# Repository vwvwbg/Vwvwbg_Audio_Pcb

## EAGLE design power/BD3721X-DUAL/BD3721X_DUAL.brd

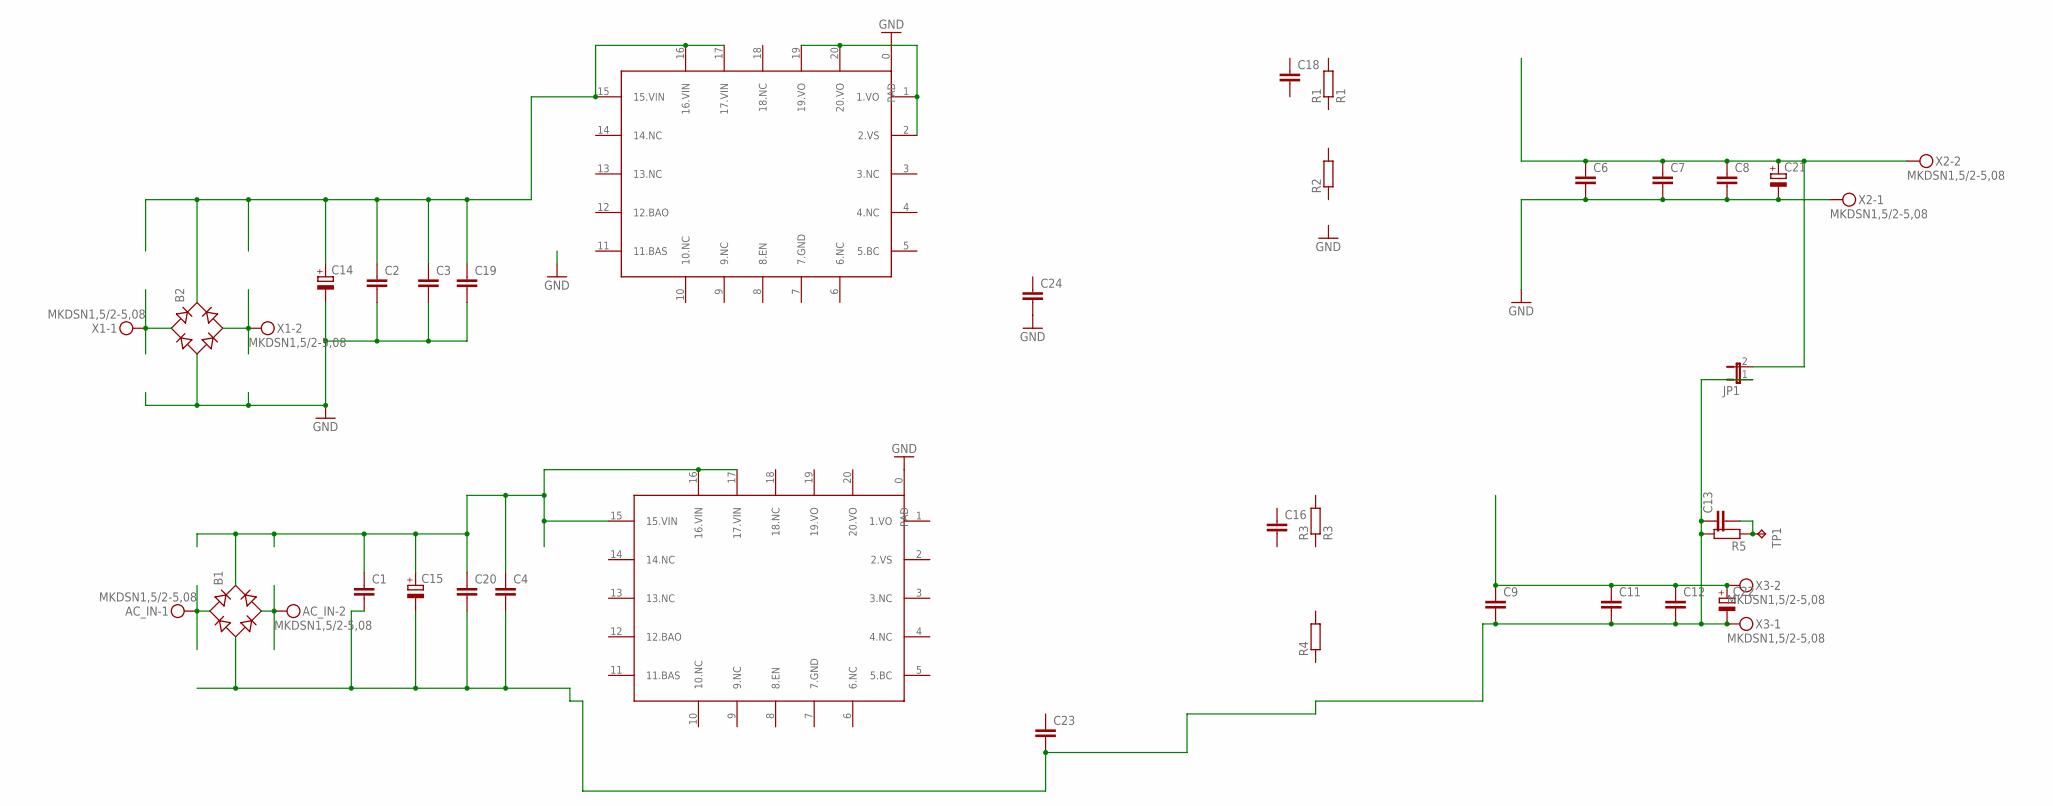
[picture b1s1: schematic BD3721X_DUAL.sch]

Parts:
AC_IN: MKDSN1,5/2-5,08
B1, B2: RB1A
C1, C2, C8, C11: C-EUC1210; C1210
C3, C4, C7, C12: C-EUC0805; C0805
C6, C9, C16, C18, C19, C20, C23, C24: C-EUC0603; C0603
C13: C-EU075-042X103; C075-042X103
C14, C15: CPOL-EUE5-13; E5-13
C21, C22: CPOL-EUE3.5-8; E3,5-8
JP1: JP1E; JP1
R1: R1; R0805
R2, R4: R-EU_R0805; R0805
R3: R3; R0805
R5: R-EU_0207/12; 0207/12
TP1: TPPAD1-13; P1-13
U$1, U$2: BD37210QFN20; QFN20-4X4MM
X1, X2, X3: MKDSN1,5/2-5,08

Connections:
GND: B2.-, C2.2, C3.2, C6.2, C7.2, C8.2, C14.-, C19.2, C21.-, C24.2, U$1.0 (PAD), U$2.0 (PAD), X2.1
GND2: B1.-, C1.2, C4.2, C9.2, C11.2, C12.2, C13.1, C15.-, C20.2, C22.-, C23.2, JP1.1, R5.2, X3.1
unnamed: AC_IN.1, B1.AC1
unnamed: B2.+, C2.1, C3.1, C14.+, C19.1, U$1.15 (15.VIN), U$1.16 (16.VIN), U$1.17 (17.VIN)
unnamed: U$1.1 (1.VO), U$1.2 (2.VS), U$1.19 (19.VO), U$1.20 (20.VO)
unnamed: B2.AC2, X1.2
unnamed: B2.AC1, X1.1
unnamed: AC_IN.2, B1.AC2
unnamed: C13.2, R5.1, TP1.TP
unnamed: B1.+, C1.1, C4.1, C15.+, C20.1, U$2.15 (15.VIN), U$2.16 (16.VIN), U$2.17 (17.VIN)
V+: C6.1, C7.1, C8.1, C21.+, JP1.2, X2.2
V-: C9.1, C11.1, C12.1, C22.+, X3.2

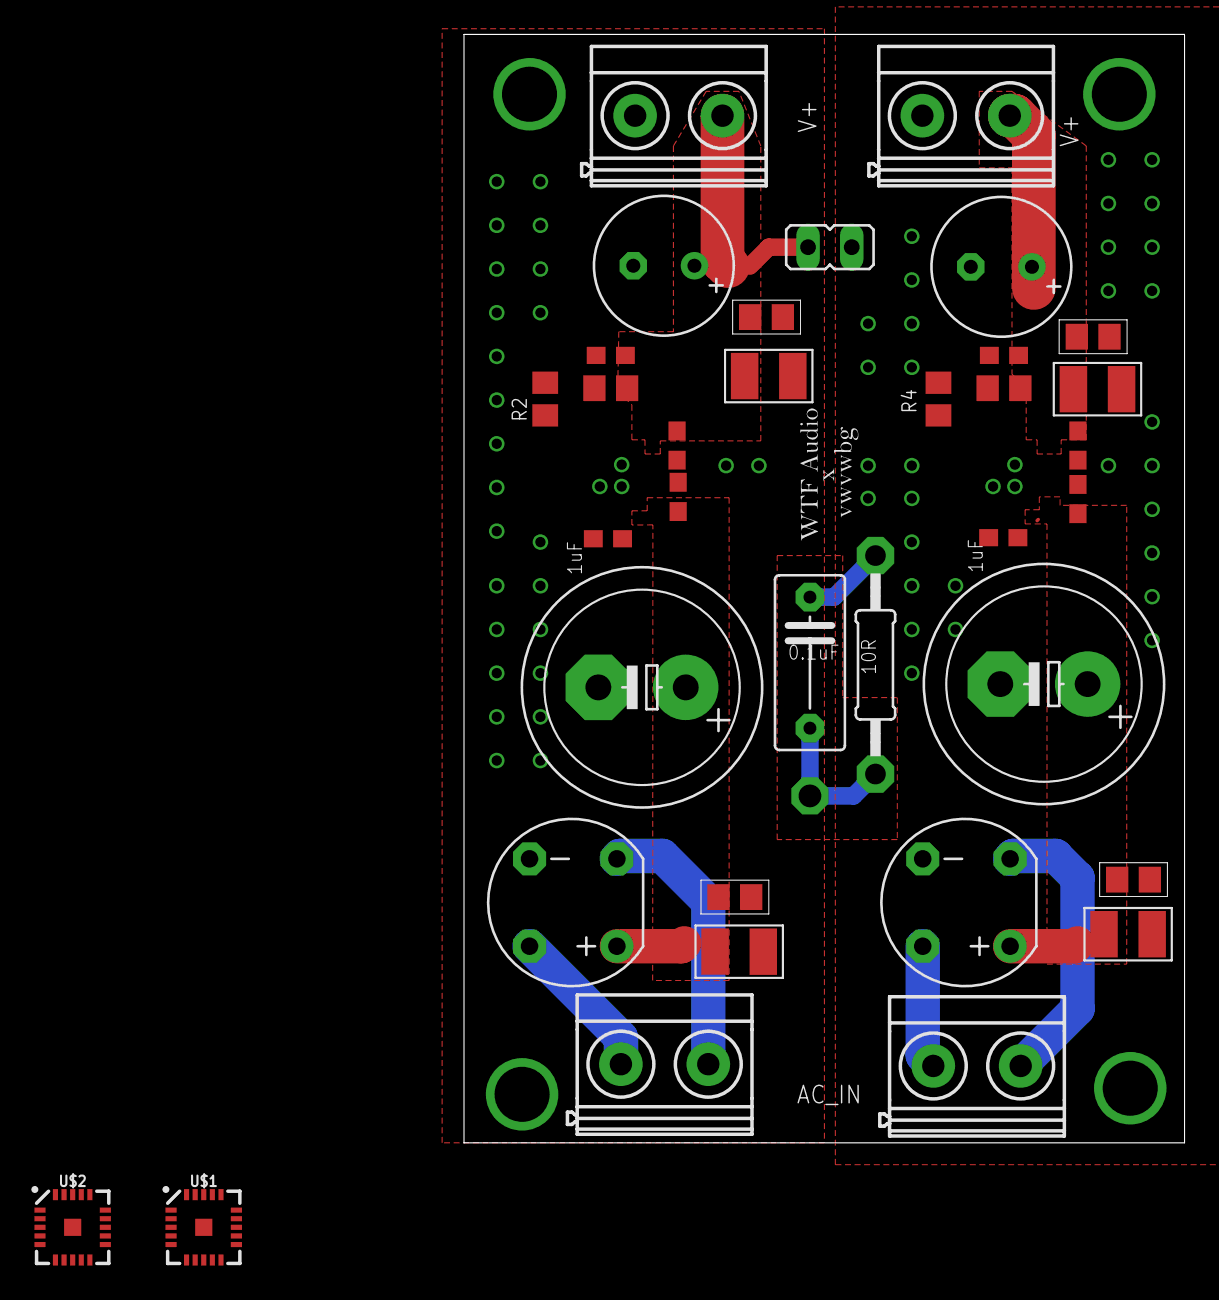
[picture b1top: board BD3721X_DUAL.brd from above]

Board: 2 copper layers, 41.9 x 64.4 mm, 36 parts (0 on the bottom side), 12 nets.

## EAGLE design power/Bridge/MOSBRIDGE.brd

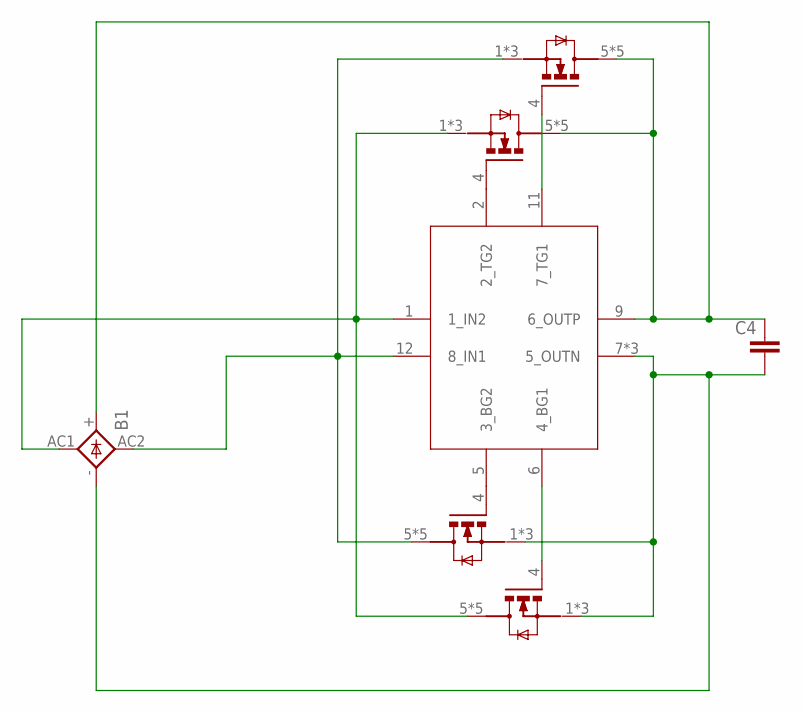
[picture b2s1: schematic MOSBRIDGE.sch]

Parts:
B1: GBU4; GBU4S
C4: 47uF; C1206
Q1, Q2, Q3, Q4: MOS_SMDTDSON-8; PG-TDSON-8
U$1: LT4320MSOP; LT4320_MSOP

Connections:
unnamed: Q2.4 (G), U$1.11 (7_TG1)
unnamed: B1.+, C4.1, Q1.5 (D), Q1.6 (D), Q1.7 (D), Q1.8 (D), Q1.TH (D), Q2.5 (D), Q2.6 (D), Q2.7 (D), Q2.8 (D), Q2.TH (D), U$1.9 (6_OUTP)
unnamed: Q1.4 (G), U$1.2 (2_TG2)
unnamed: Q4.4 (G), U$1.6 (4_BG1)
unnamed: B1.-, C4.2, Q3.1 (S), Q3.2 (S), Q3.3 (S), Q4.1 (S), Q4.2 (S), Q4.3 (S), U$1.7 (5_OUTN), U$1.EXP (5_OUTN), U$1.EXP1 (5_OUTN)
unnamed: B1.AC1 (AC2), Q1.1 (S), Q1.2 (S), Q1.3 (S), Q4.5 (D), Q4.6 (D), Q4.7 (D), Q4.8 (D), Q4.TH (D), U$1.1 (1_IN2)
unnamed: B1.AC2 (AC1), Q2.1 (S), Q2.2 (S), Q2.3 (S), Q3.5 (D), Q3.6 (D), Q3.7 (D), Q3.8 (D), Q3.TH (D), U$1.12 (8_IN1)
unnamed: Q3.4 (G), U$1.5 (3_BG2)

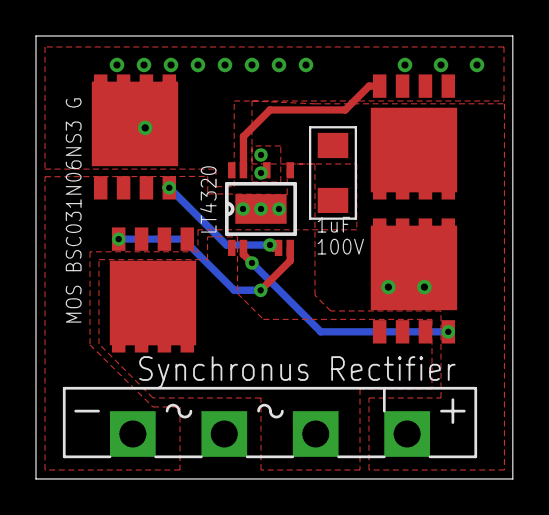
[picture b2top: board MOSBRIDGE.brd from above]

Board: 2 copper layers, 26.5 x 24.6 mm, 7 parts (0 on the bottom side), 8 nets.

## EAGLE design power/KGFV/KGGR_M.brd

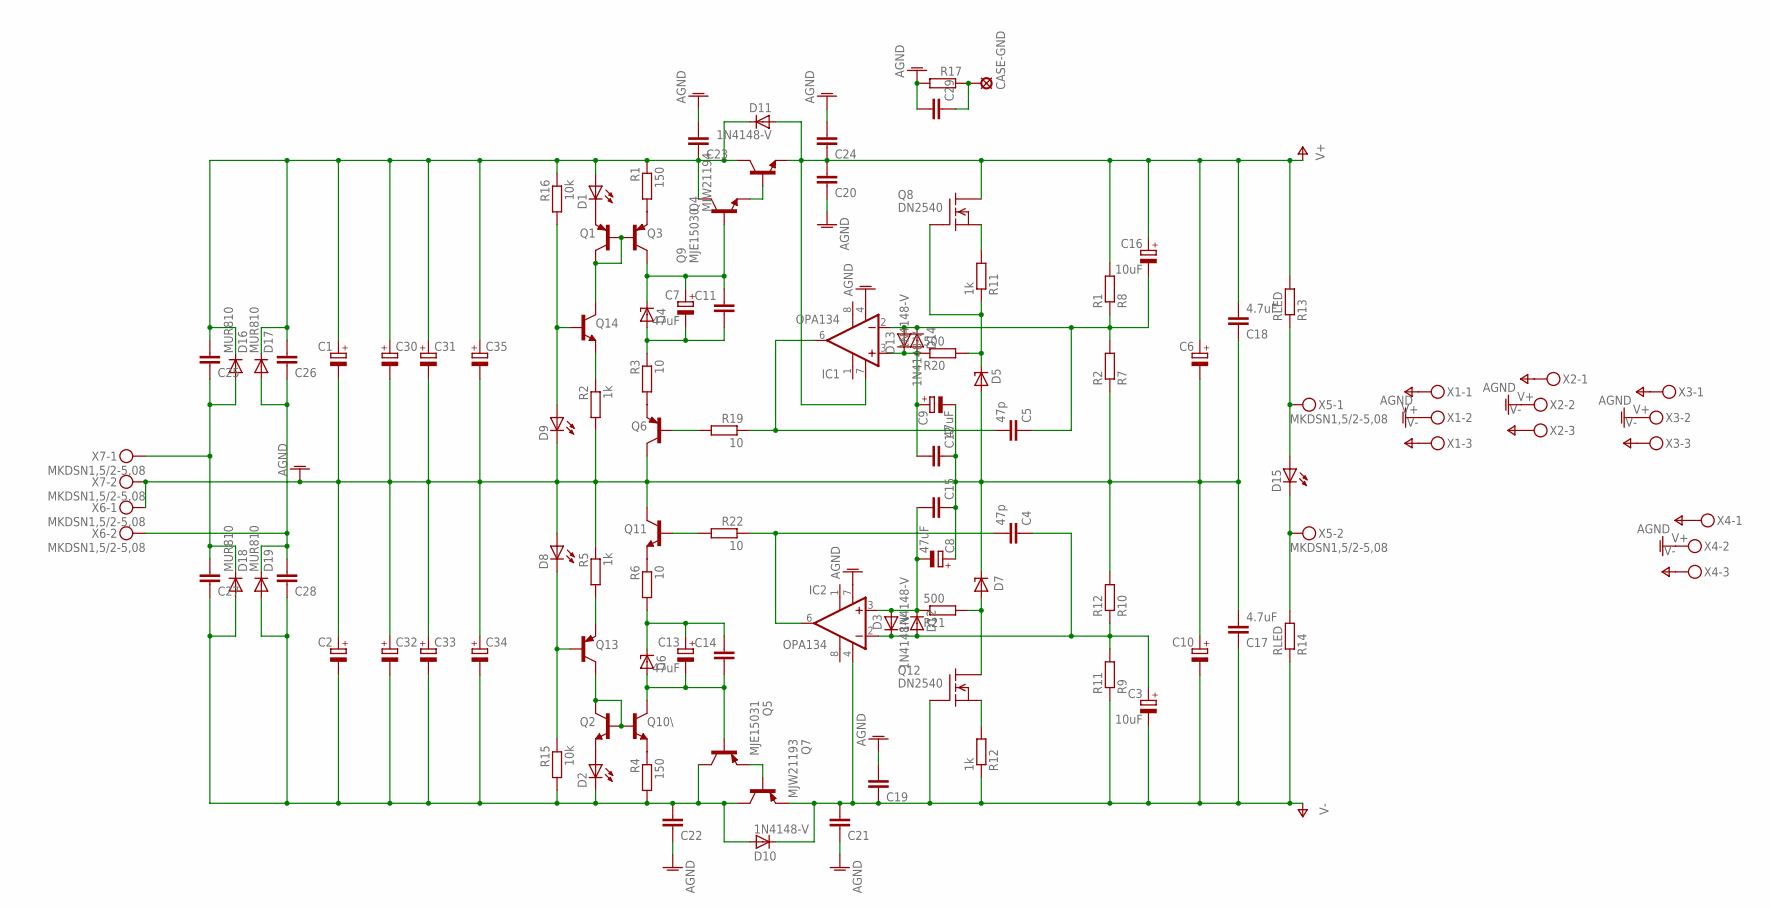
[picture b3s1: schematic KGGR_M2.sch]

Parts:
C1, C2: CPOL-EUE10-35; EB35D
C3, C16: 10uF; E5-8,5
C4, C5: 47p; C025_050-025X075
C6, C10, C30, C31, C32, C33, C34, C35: CPOL-EUE7.5-18; E7,5-18
C7, C8, C9, C13: 47uF; E5-8,5
C11, C12, C14, C15, C19, C20, C21, C24, C25, C26, C27, C28: C-EU050-035X075; C050-035X075
C17, C18: 4.7uF; C050-075X075
C22, C23: C-EU050-075X075; C050-075X075
C29: C-EU102_152-062X184; C102_152-062X184
CASE-GND: SE14
D1, D2, D8, D9, D15: LED5MM
D3, D10, D11, D12, D13, D14: 1N4148-V; 1N4148
D4, D6: 1N4728; DO41Z10
D5, D7: LT1021; DIL08
D16, D17, D18, D19: MUR810; TO220ACS
IC1, IC2: OPA134; DIL08
Q1, Q3, Q6, Q13: MPSA92-PNP-TO92-EBC; TO92-EBC
Q2, Q10\, Q11, Q14: MPSA42-NPN-TO92-EBC; TO92-EBC
Q4: MJW21194; TO-264
Q5: MJE15031; TO220KG
Q7: MJW21193; TO-264
Q8, Q12: DN2540; TO92-
Q9: MJE15030; TO220KG
R1, R4: 150; 0309/12
R2, R5, R11, R12: 1k; 0309/12
R3, R6, R19, R22: 10; 0309/12
R7: R2; 0309/12
R8: R1; 0309/12
R9: R11; 0309/12
R10: R12; 0309/12
R13, R14: RLED; 0309/12
R15, R16: 10k; 0309/12
R17: R-EU_0617/22; 0617/22
R20, R21: 500; 0309/12
X1, X2, X3, X4: MKDSN1,5/3-5,08
X5, X6, X7: MKDSN1,5/2-5,08

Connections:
unnamed: Q1.B, Q1.C, Q3.B, Q14.C
unnamed: D1.K (C), Q1.E
unnamed: Q3.E, R1.2
unnamed: C7.+, C11.1, D4.C, Q3.C, Q9.1 (B)
unnamed: C7.-, C11.2, D4.A, R3.1
unnamed: Q6.E, R3.2
unnamed: Q14.E, R2.1
unnamed: D9.A, Q14.B, R16.2
unnamed: C8.-, C15.2, D3.A, D12.C, IC2.3 (+IN), R21.1
unnamed: Q13.E, R5.2
unnamed: D8.K (C), Q13.B, R15.1
unnamed: Q11.E, R6.1
unnamed: C13.+, C14.1, D6.C, R6.2
unnamed: C13.-, C14.2, D6.A, Q5.1 (B), Q10\.C
unnamed: Q2.B, Q2.C, Q10\.B, Q13.C
unnamed: Q5.3 (E), Q7.B
unnamed: Q10\.E, R4.1
unnamed: D2.A, Q2.E
unnamed: Q4.B, Q9.3 (E)
unnamed: C5.2, C5.3 (2), IC1.6 (OUT), R19.1
unnamed: C4.2, C4.3 (2), IC2.6 (OUT), R22.1
unnamed: Q11.B, R22.2
unnamed: Q6.B, R19.2
unnamed: C5.1, C16.-, D13.A, D14.C, IC1.2 (-IN), R7.2, R8.1
unnamed: Q12.3 (S), R12.2
unnamed: D5.6 (OUT), Q8.2 (G), R11.1, R20.2
unnamed: C9.+, C12.2, D13.C, D14.A, IC1.3 (+IN), R20.1
unnamed: D15.K (C), R14.2, X5.2
unnamed: D7.4 (GND), Q12.1 (D), R21.2
unnamed: C3.+, C4.1, D3.C, D12.A, IC2.2 (-IN), R9.2, R10.1
unnamed: Q8.3 (S), R11.2
unnamed: D15.A, R13.1, X5.1
unnamed: C29.1, CASE-GND.MP, R17.1
V+: C6.+, C16.+, C18.2, C20.2, C24.1, D11.A, IC1.7 (V+), Q4.E, Q8.1 (D), R8.2, R13.2, X1.1, X2.1, X3.1, X4.1
V-: C3.-, C10.-, C17.1, C19.1, C21.2, D10.C, IC2.4 (V-), Q7.E, Q12.2 (G), R9.1, R12.1, R14.1, X1.3, X2.3, X3.3, X4.3

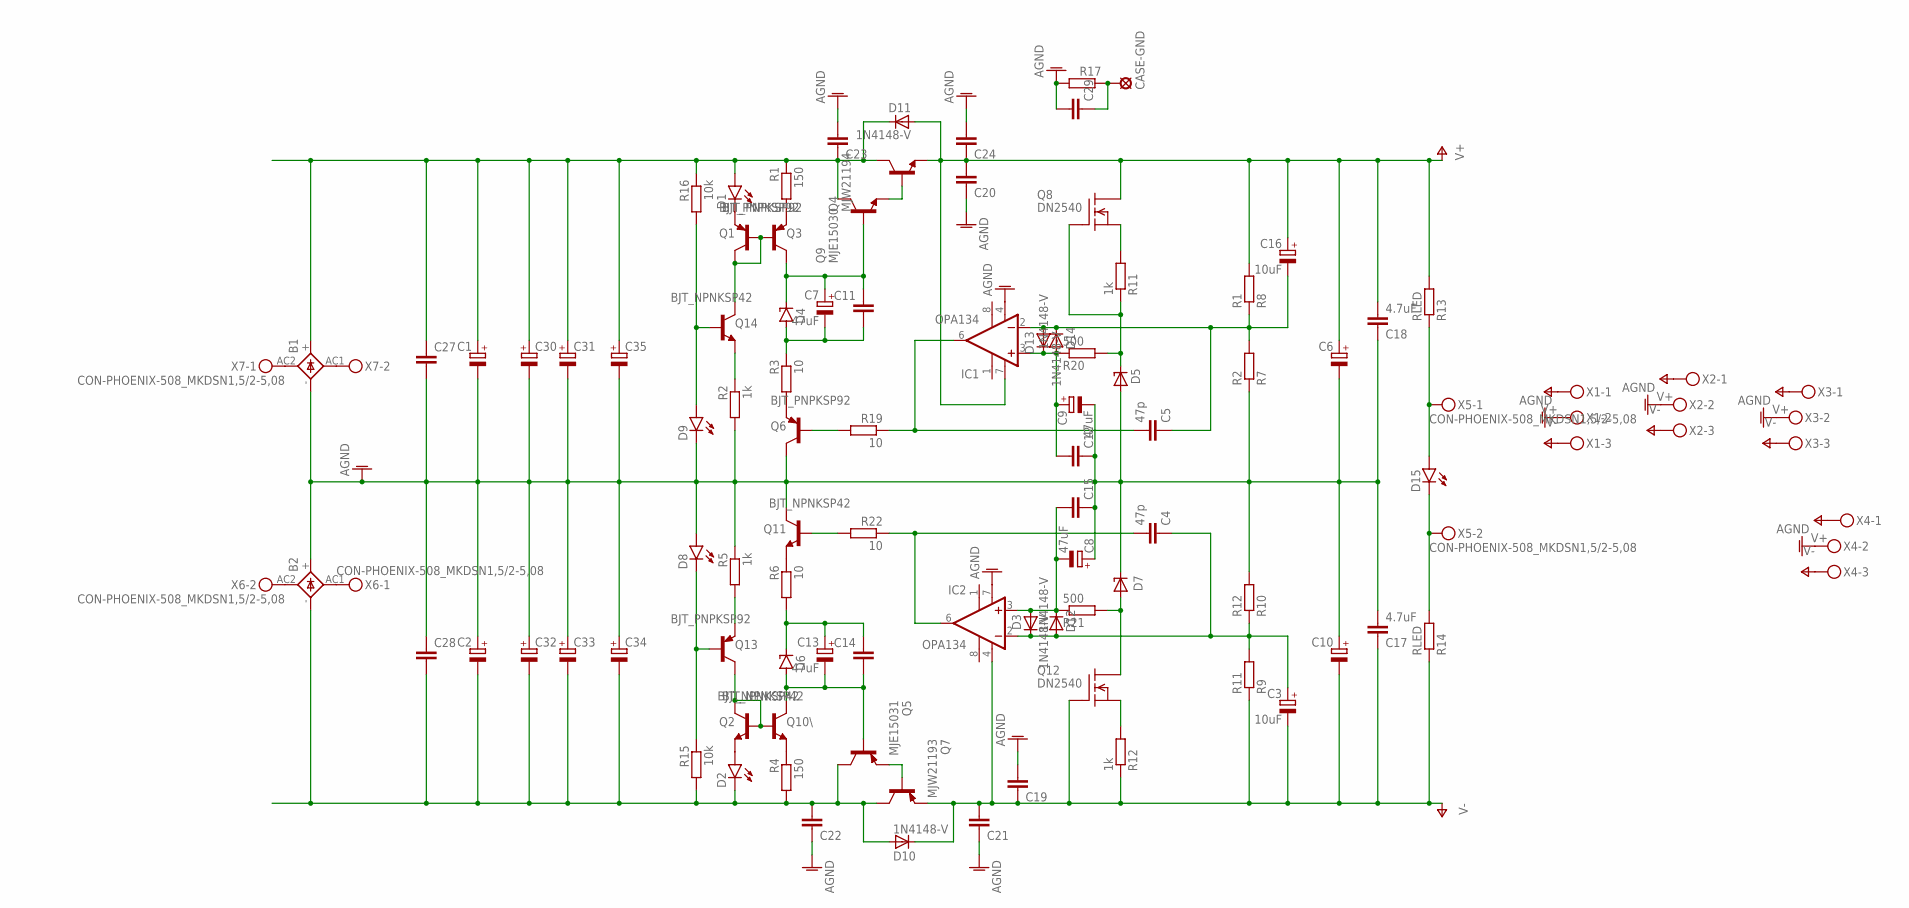
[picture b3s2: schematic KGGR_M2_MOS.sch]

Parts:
B1, B2: GBU4; GBU4S
C1, C2: CPOL-EUE10-35; EB35D
C3, C16: 10uF; E5-8,5
C4, C5: 47p; C025_050-025X075
C6, C10, C30, C31, C32, C33, C34, C35: CPOL-EUE7.5-18; E7,5-18
C7, C8, C9, C13: 47uF; E5-8,5
C11, C12, C14, C15, C19, C20, C21, C24: C-EU050-035X075; C050-035X075
C17, C18: 4.7uF; C050-075X075
C22, C23: C-EU050-075X075; C050-075X075
C27, C28, C29: C-EU102_152-062X184; C102_152-062X184
CASE-GND: SE14
D1, D2, D8, D9, D15: LED5MM
D3, D10, D11, D12, D13, D14: 1N4148-V; 1N4148
D4, D6: 1N4728; DO41Z10
D5, D7: LT1021; DIL08
IC1, IC2: OPA134; DIL08
Q1, Q3, Q6, Q13: BJT_PNPKSP92; TRANSISTOR_TO92-EBC_P
Q2, Q10\, Q11, Q14: BJT_NPNKSP42; TRANSISTOR_TO92-EBC_N
Q4: MJW21194; TRANSISTOR_TO247_BCE_N
Q5: MJE15031; TO220KG
Q7: MJW21193; TRANSISTOR_TO247_BCE_P
Q8, Q12: DN2540; TO92-
Q9: MJE15030; TO220KG
R1, R4: 150; 0309/12
R2, R5, R11, R12: 1k; 0309/12
R3, R6, R19, R22: 10; 0309/12
R7: R2; 0309/12
R8: R1; 0309/12
R9: R11; 0309/12
R10: R12; 0309/12
R13, R14: RLED; 0309/12
R15, R16: 10k; 0309/12
R17: R-EU_0617/22; 0617/22
R20, R21: 500; 0309/12
X1, X2, X3, X4: CON-PHOENIX-508_MKDSN1,5/3-5,08
X5, X6, X7: CON-PHOENIX-508_MKDSN1,5/2-5,08

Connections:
unnamed: Q1.B, Q1.C, Q3.B, Q14.C
unnamed: D1.K (C), Q1.E
unnamed: Q3.E, R1.2
unnamed: C7.+, C11.1, D4.C, Q3.C, Q9.1 (B)
unnamed: C7.-, C11.2, D4.A, R3.1
unnamed: Q6.E, R3.2
unnamed: Q14.E, R2.1
unnamed: D9.A, Q14.B, R16.2
unnamed: C8.-, C15.2, D3.A, D12.C, IC2.3 (+IN), R21.1
unnamed: Q13.E, R5.2
unnamed: D8.K (C), Q13.B, R15.1
unnamed: Q11.E, R6.1
unnamed: C13.+, C14.1, D6.C, R6.2
unnamed: C13.-, C14.2, D6.A, Q5.1 (B), Q10\.C
unnamed: Q2.B, Q2.C, Q10\.B, Q13.C
unnamed: Q5.3 (E), Q7.B
unnamed: Q10\.E, R4.1
unnamed: D2.A, Q2.E
unnamed: Q4.B, Q9.3 (E)
unnamed: C5.2, C5.3 (2), IC1.6 (OUT), R19.1
unnamed: C4.2, C4.3 (2), IC2.6 (OUT), R22.1
unnamed: Q11.B, R22.2
unnamed: Q6.B, R19.2
unnamed: C5.1, C16.-, D13.A, D14.C, IC1.2 (-IN), R7.2, R8.1
unnamed: Q12.3 (S), R12.2
unnamed: D5.6 (OUT), Q8.2 (G), R11.1, R20.2
unnamed: C9.+, C12.2, D13.C, D14.A, IC1.3 (+IN), R20.1
unnamed: D15.K (C), R14.2, X5.2
unnamed: D7.4 (GND), Q12.1 (D), R21.2
unnamed: C3.+, C4.1, D3.C, D12.A, IC2.2 (-IN), R9.2, R10.1
unnamed: Q8.3 (S), R11.2
unnamed: D15.A, R13.1, X5.1
unnamed: C29.1, CASE-GND.MP, R17.1
V+: C6.+, C16.+, C18.2, C20.2, C24.1, D11.A, IC1.7 (V+), Q4.E, Q8.1 (D), R8.2, R13.2, X1.1, X2.1, X3.1, X4.1
V-: C3.-, C10.-, C17.1, C19.1, C21.2, D10.C, IC2.4 (V-), Q7.E, Q12.2 (G), R9.1, R12.1, R14.1, X1.3, X2.3, X3.3, X4.3

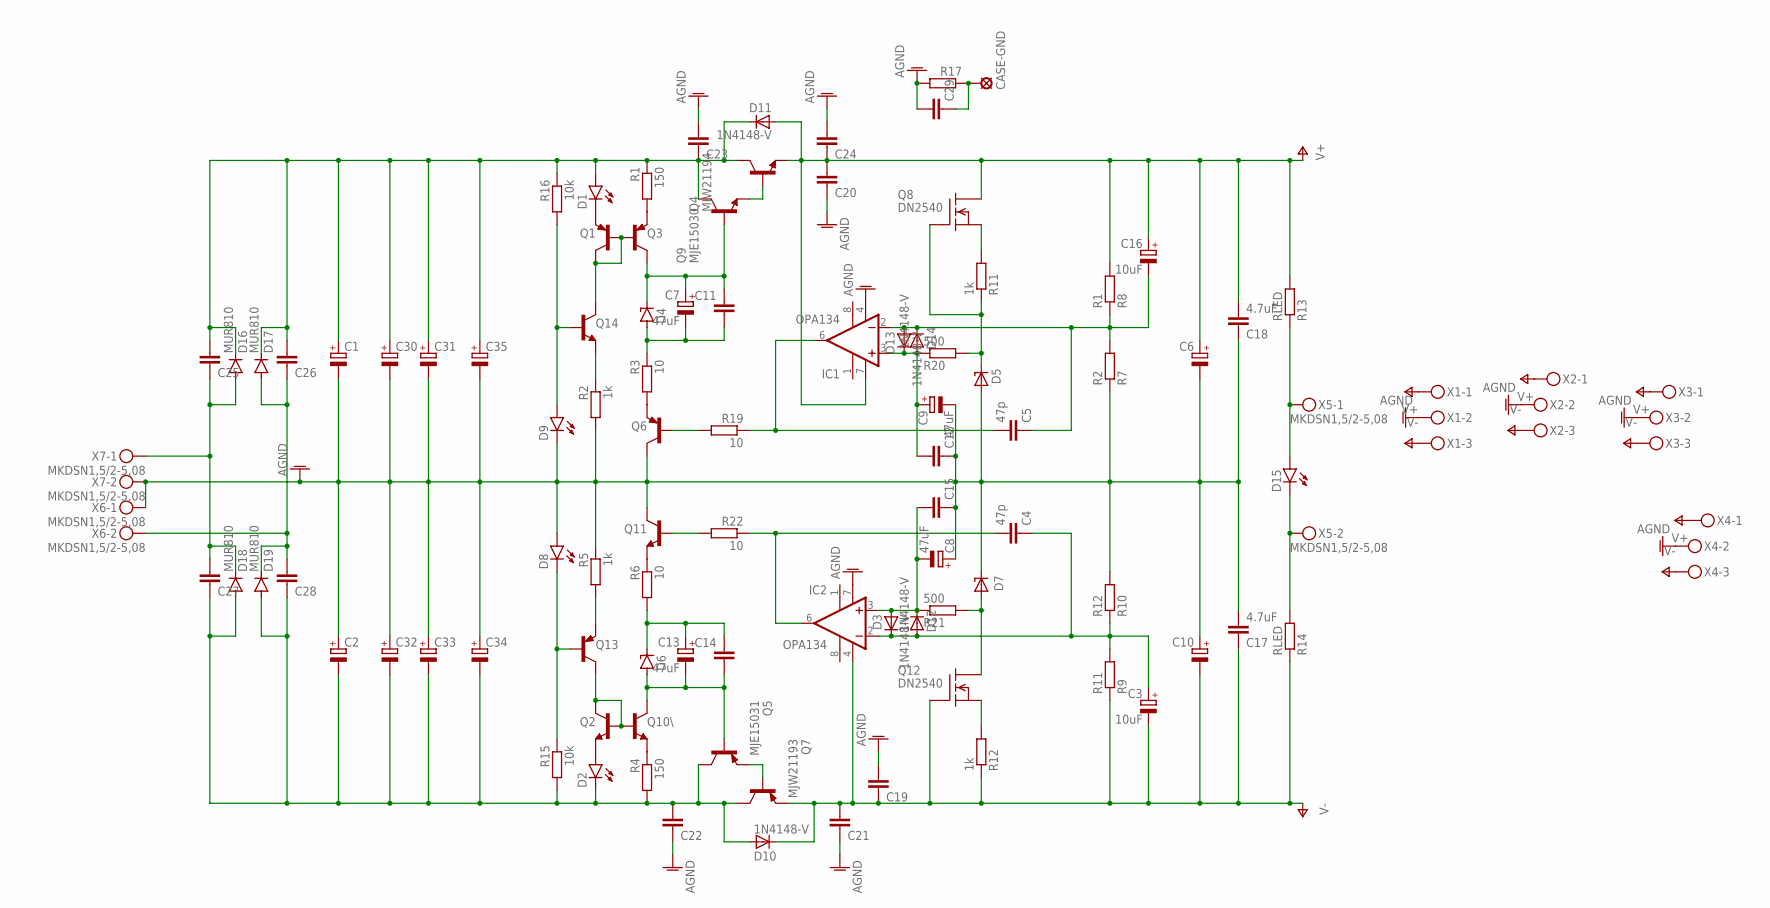
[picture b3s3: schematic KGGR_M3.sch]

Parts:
C1, C2, C6, C10, C30, C31, C32, C33, C34, C35: CPOL-EUE7.5-18; E7,5-18
C3, C16: 10uF; E5-8,5
C4, C5: 47p; C025_050-025X075
C7, C8, C9, C13: 47uF; E5-8,5
C11, C12, C14, C15, C19, C20, C21, C24, C25, C26, C27, C28: C-EU050-035X075; C050-035X075
C17, C18: 4.7uF; C050-075X075
C22, C23: C-EU050-075X075; C050-075X075
C29: C-EU102_152-062X184; C102_152-062X184
CASE-GND: SE14
D1, D2, D8, D9, D15: LED5MM
D3, D10, D11, D12, D13, D14: 1N4148-V; 1N4148
D4, D6: 1N4728; DO41Z10
D5, D7: LT1021; DIL08
D16, D17, D18, D19: MUR810; TO220ACS
IC1, IC2: OPA134; DIL08
Q1, Q3, Q6, Q13: MPSA92-PNP-TO92-EBC; TO92-EBC
Q2, Q10\, Q11, Q14: MPSA42-NPN-TO92-EBC; TO92-EBC
Q4: MJW21194; TO-264
Q5: MJE15031; TO220KG
Q7: MJW21193; TO-264
Q8, Q12: DN2540; TO92-
Q9: MJE15030; TO220KG
R1, R4: 150; 0309/12
R2, R5, R11, R12: 1k; 0309/12
R3, R6, R19, R22: 10; 0309/12
R7: R2; 0309/12
R8: R1; 0309/12
R9: R11; 0309/12
R10: R12; 0309/12
R13, R14: RLED; 0309/12
R15, R16: 10k; 0309/12
R17: R-EU_0617/22; 0617/22
R20, R21: 500; 0309/12
X1, X2, X3, X4: MKDSN1,5/3-5,08
X5, X6, X7: MKDSN1,5/2-5,08

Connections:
unnamed: Q1.B, Q1.C, Q3.B, Q14.C
unnamed: D1.K (C), Q1.E
unnamed: Q3.E, R1.2
unnamed: C7.+, C11.1, D4.C, Q3.C, Q9.1 (B)
unnamed: C7.-, C11.2, D4.A, R3.1
unnamed: Q6.E, R3.2
unnamed: Q14.E, R2.1
unnamed: D9.A, Q14.B, R16.2
unnamed: C8.-, C15.2, D3.A, D12.C, IC2.3 (+IN), R21.1
unnamed: Q13.E, R5.2
unnamed: D8.K (C), Q13.B, R15.1
unnamed: Q11.E, R6.1
unnamed: C13.+, C14.1, D6.C, R6.2
unnamed: C13.-, C14.2, D6.A, Q5.1 (B), Q10\.C
unnamed: Q2.B, Q2.C, Q10\.B, Q13.C
unnamed: Q5.3 (E), Q7.B
unnamed: Q10\.E, R4.1
unnamed: D2.A, Q2.E
unnamed: Q4.B, Q9.3 (E)
unnamed: C5.2, C5.3 (2), IC1.6 (OUT), R19.1
unnamed: C4.2, C4.3 (2), IC2.6 (OUT), R22.1
unnamed: Q11.B, R22.2
unnamed: Q6.B, R19.2
unnamed: C5.1, C16.-, D13.A, D14.C, IC1.2 (-IN), R7.2, R8.1
unnamed: Q12.3 (S), R12.2
unnamed: D5.6 (OUT), Q8.2 (G), R11.1, R20.2
unnamed: C9.+, C12.2, D13.C, D14.A, IC1.3 (+IN), R20.1
unnamed: D15.K (C), R14.2, X5.2
unnamed: D7.4 (GND), Q12.1 (D), R21.2
unnamed: C3.+, C4.1, D3.C, D12.A, IC2.2 (-IN), R9.2, R10.1
unnamed: Q8.3 (S), R11.2
unnamed: D15.A, R13.1, X5.1
unnamed: C29.1, CASE-GND.MP, R17.1
V+: C6.+, C16.+, C18.2, C20.2, C24.1, D11.A, IC1.7 (V+), Q4.E, Q8.1 (D), R8.2, R13.2, X1.1, X2.1, X3.1, X4.1
V-: C3.-, C10.-, C17.1, C19.1, C21.2, D10.C, IC2.4 (V-), Q7.E, Q12.2 (G), R9.1, R12.1, R14.1, X1.3, X2.3, X3.3, X4.3

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
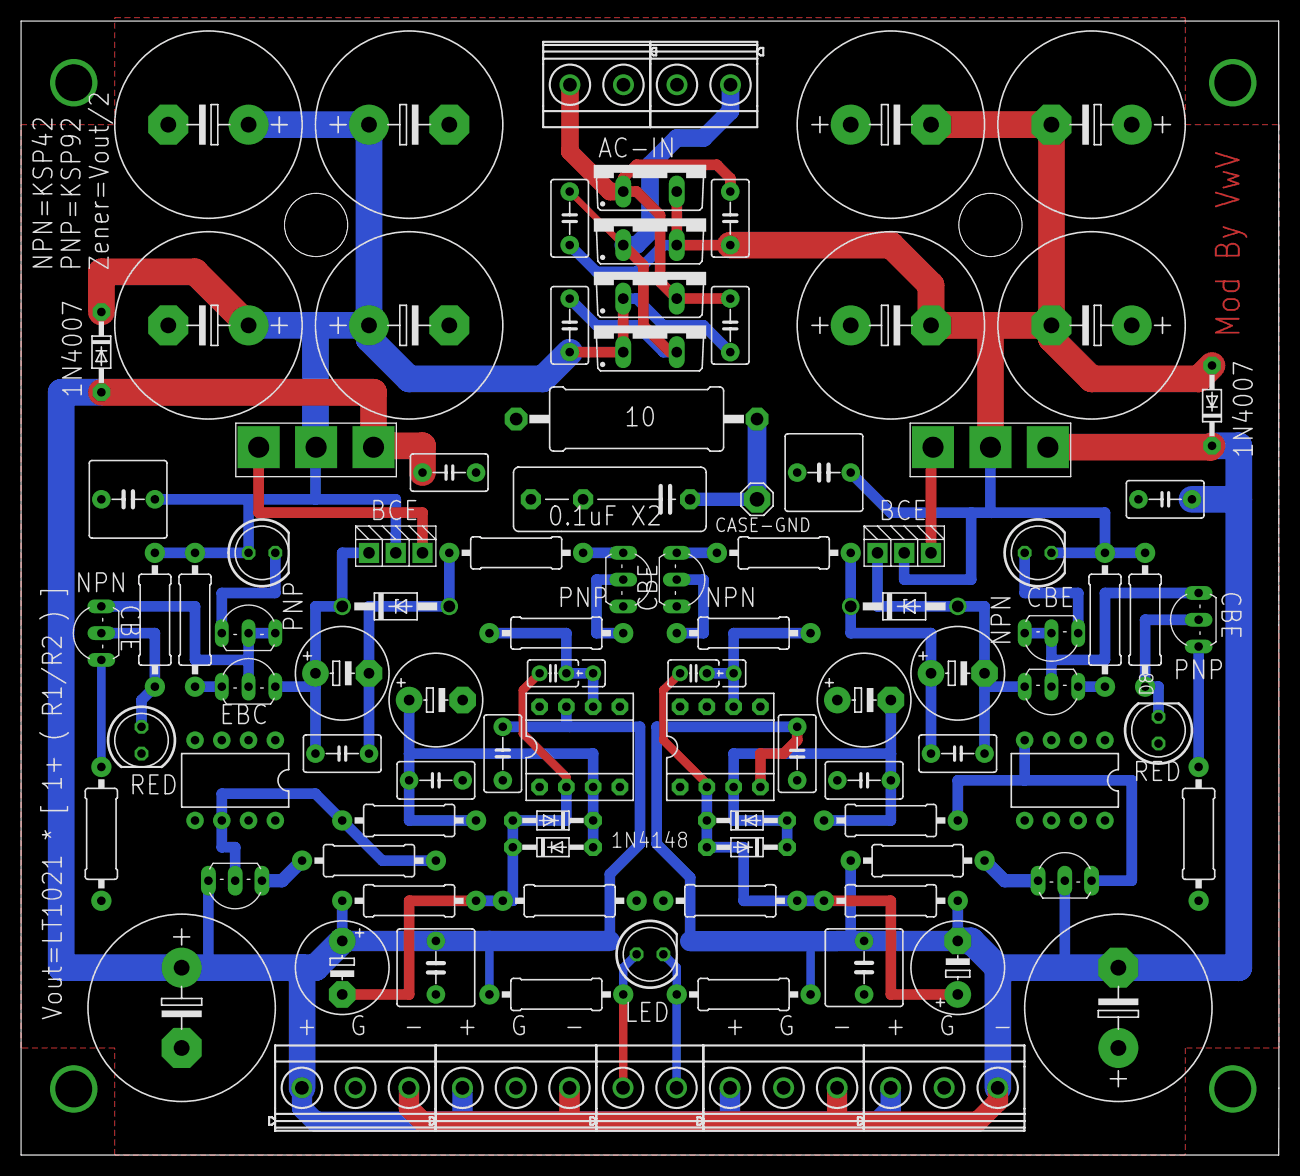
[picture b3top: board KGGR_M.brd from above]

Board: 2 copper layers, 119.4 x 107.6 mm, 99 parts (0 on the bottom side), 40 nets.

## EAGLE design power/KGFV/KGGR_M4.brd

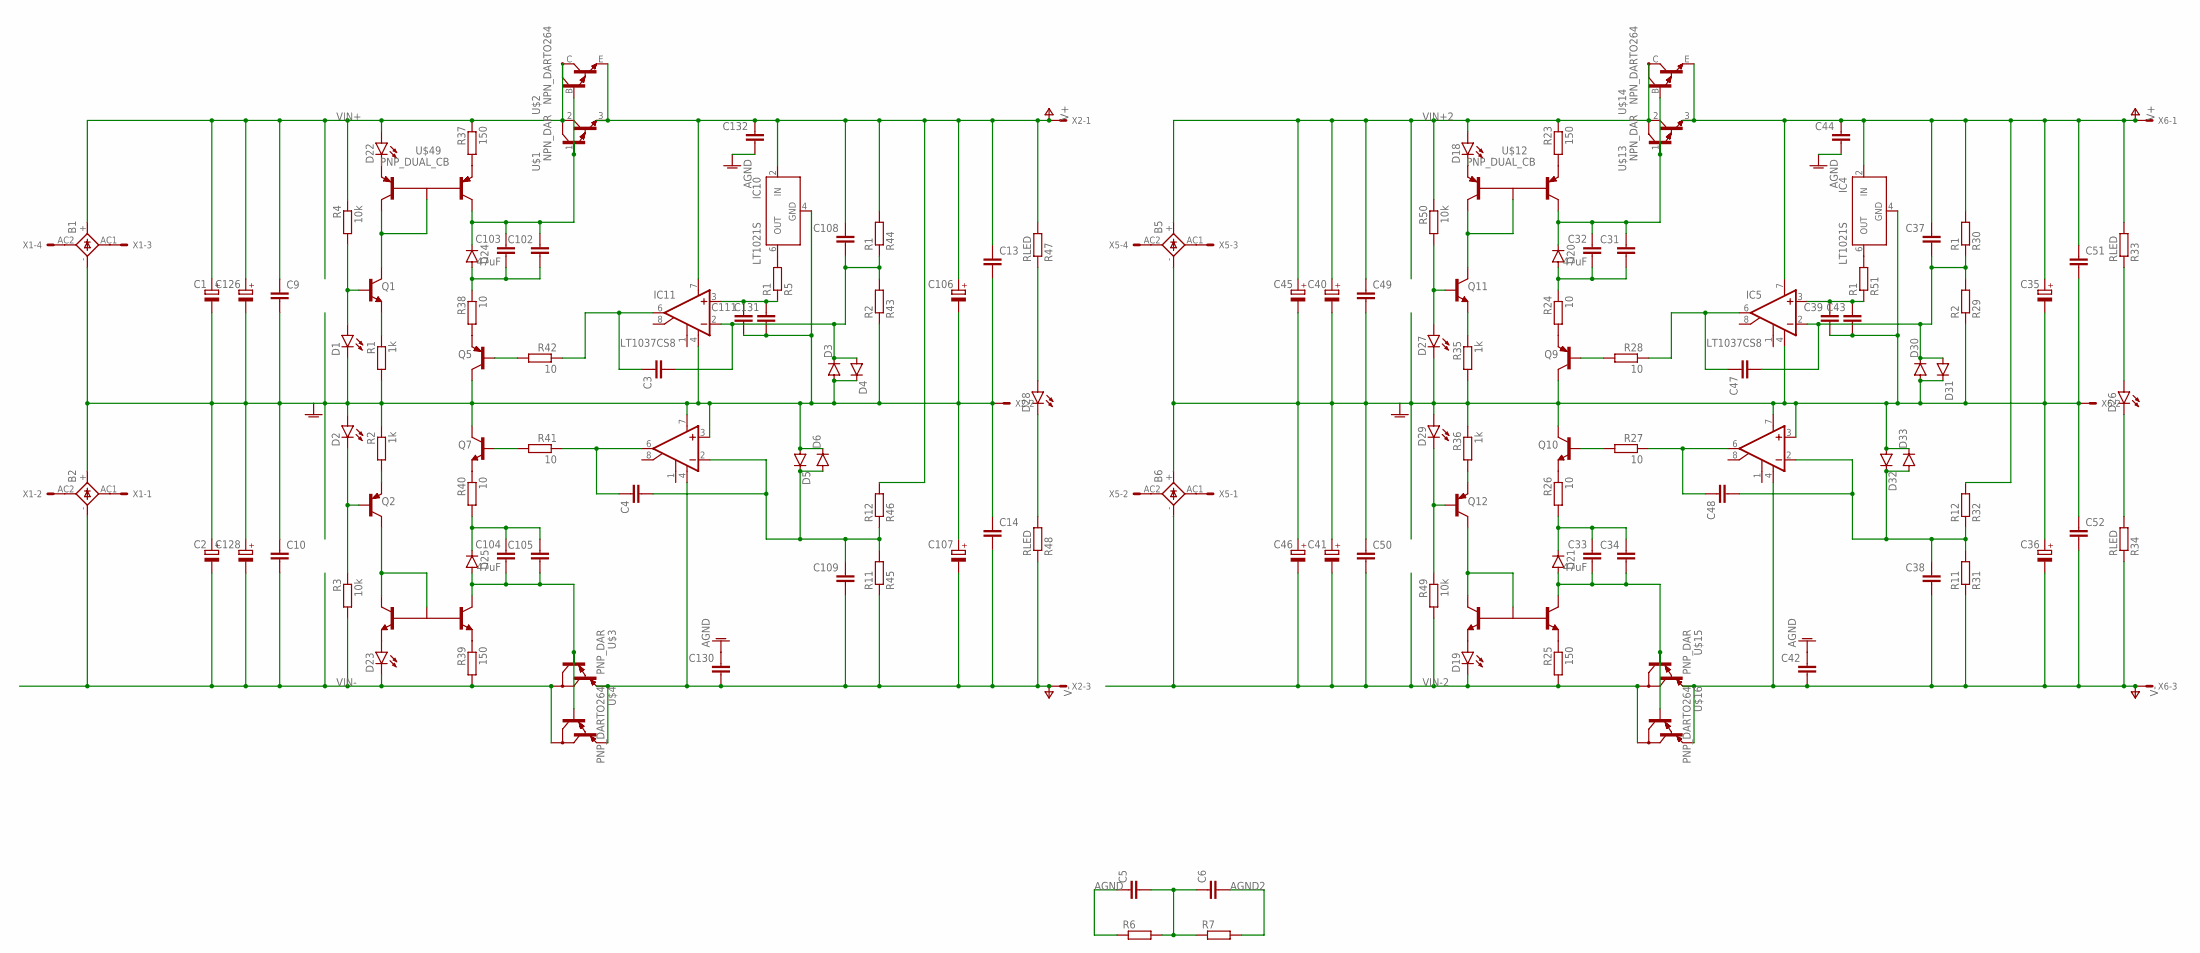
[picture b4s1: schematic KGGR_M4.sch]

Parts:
B1, B2, B5, B6: GBU4; GBU4S
C1, C2, C40, C41, C45, C46, C126, C128: CPOL-EUE7.5-18; E7,5-18
C3, C4, C31, C34, C37, C38, C39, C42, C44, C47, C48, C102, C105, C108, C109, C111, C130, C132: C-EUC0805; C0805
C5, C6: C-EU075-042X103; C075-042X103
C9, C10, C13, C14, C49, C50, C51, C52: C-EU050-050X075; C050-050X075
C32, C33, C103, C104: 47uF; C1206
C35, C36, C106, C107: CPOL-EUE5-10.5; E5-10,5
C43, C131: C-EUC1206; C1206
D1, D2, D18, D19, D22, D23, D26, D27, D28, D29: LEDVWV1206; LED_SML1206
D3, D4, D5, D6, D30, D31, D32, D33: DIODE-SOD80C; SOD80C
D20, D24: TZMC10; SOD80C
D21, D25: TZAMC10; SOD80C
IC4, IC10: LT1021S; SOIC8
IC5, IC6, IC11, IC12: LT1037CS8; SOIC8
Q1, Q7, Q10, Q11: TRANSISTOR_BC847CLT1-NPN-SOT23-BEC; TRANSISTOR_SOT23-BEC
Q2, Q5, Q9, Q12: TRANSISTOR_BC857C-PNP-SOT23-BEC; TRANSISTOR_SOT23-BEC
R1, R2, R35, R36: 1k; MINI_MELF-0204W
R3, R4, R49, R50: 10k; MINI_MELF-0204W
R5, R30, R44, R51: R1; MINI_MELF-0204W
R6, R7: R-EU_R2512; R2512
R23, R25, R37, R39: 150; MINI_MELF-0204W
R24, R26, R27, R28, R38, R40, R41, R42: 10; MINI_MELF-0204W
R29, R43: R2; MINI_MELF-0204W
R31, R45: R11; MINI_MELF-0204W
R32, R46: R12; MINI_MELF-0204W
R33, R34, R47, R48: RLED; MINI_MELF-0204W
U$1, U$13: NPN_DAR; TRANSISTOR_TO220KG
U$2, U$14: NPN_DARTO264; TO264_TO-264
U$3, U$15: PNP_DAR; TRANSISTOR_TO220KG
U$4, U$16: PNP_DARTO264; TO264_TO-264
U$11, U$48: NPN_DUAL_CBSOT-25-5; SOT25
U$12, U$49: PNP_DUAL_CB; SOT25
X1, X5: KK-156-4
X2, X6: KK-156-3

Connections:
AGND: B1.-, B2.+, C1.-, C2.+, C5.1, C9.2, C10.1, C13.2, C14.1, C106.-, C107.+, C111.2, C126.-, C128.+, C130.1, C131.2, C132.2, D1.C, D2.A, D3.A, D4.C, D5.A, D6.C, IC10.4 (GND), IC11.4 (V-), IC12.3 (+IN), IC12.7 (V+), Q5.C, Q7.C, R1.2, R2.1, R6.1, R43.1, X2.2
AGND2: B5.-, B6.+, C6.2, C35.-, C36.+, C39.2, C40.-, C41.+, C42.1, C43.2, C44.2, C45.-, C46.+, C49.2, C50.1, C51.2, C52.1, D27.C, D29.A, D30.A, D31.C, D32.A, D33.C, IC4.4 (GND), IC5.4 (V-), IC6.3 (+IN), IC6.7 (V+), Q9.C, Q10.C, R7.2, R29.1, R35.2, R36.1, X6.2
unnamed: B1.AC2 (AC1), X1.4
unnamed: B1.AC1 (AC2), X1.3
unnamed: B2.AC2 (AC1), X1.2
unnamed: B2.AC1 (AC2), X1.1
unnamed: C5.2, C6.1, R6.2, R7.1
unnamed: Q1.E, R1.1
unnamed: D1.A, Q1.B, R4.2
unnamed: Q2.E, R2.2
unnamed: D2.C, Q2.B, R3.1
unnamed: IC10.6 (OUT), R5.2
unnamed: Q11.C, U$12.2 (B), U$12.5 (C1)
unnamed: C31.1, C32.1, D20.C, U$12.4 (C2), U$13.1 (B), U$14.B
unnamed: C31.2, C32.2, D20.A, R24.1
unnamed: Q9.E, R24.2
unnamed: Q10.E, R26.1
unnamed: C33.1, C34.1, D21.C, R26.2
unnamed: C33.2, C34.2, D21.A, U$11.4 (C2), U$15.1 (B), U$16.B
unnamed: Q12.C, U$11.2 (B), U$11.5 (C1)
unnamed: Q10.B, R27.2
unnamed: Q9.B, R28.2
unnamed: C37.2, C47.2, D30.C, D31.A, IC5.2 (-IN), R29.2, R30.1
unnamed: D26.C, R34.2
unnamed: D26.A, R33.1
unnamed: C48.1, IC6.6 (OUT), R27.1
unnamed: C38.1, C48.2, D32.C, D33.A, IC6.2 (-IN), R31.2, R32.1
unnamed: C39.1, C43.1, IC5.3 (+IN), R51.1
unnamed: C47.1, IC5.6 (OUT), R28.1
unnamed: R25.1, U$11.3 (E2)
unnamed: D19.A, U$11.1 (E1)
unnamed: R23.2, U$12.3 (E2)
unnamed: D18.C, U$12.1 (E1)
unnamed: B5.AC2 (AC1), X5.4
unnamed: B5.AC1 (AC2), X5.3
unnamed: B6.AC2 (AC1), X5.2
unnamed: B6.AC1 (AC2), X5.1
unnamed: Q11.E, R35.1
unnamed: D27.A, Q11.B, R50.2
unnamed: Q12.E, R36.2
unnamed: D29.C, Q12.B, R49.1
unnamed: IC4.6 (OUT), R51.2
unnamed: Q1.C, U$49.2 (B), U$49.5 (C1)
unnamed: C102.1, C103.1, D24.C, U$1.1 (B), U$2.B, U$49.4 (C2)
unnamed: C102.2, C103.2, D24.A, R38.1
unnamed: Q5.E, R38.2
unnamed: Q7.E, R40.1
unnamed: C104.1, C105.1, D25.C, R40.2
unnamed: C104.2, C105.2, D25.A, U$3.1 (B), U$4.B, U$48.4 (C2)
unnamed: Q2.C, U$48.2 (B), U$48.5 (C1)
unnamed: Q7.B, R41.2
unnamed: Q5.B, R42.2
unnamed: C3.2, C108.2, D3.C, D4.A, IC11.2 (-IN), R43.2, R44.1
unnamed: D28.C, R48.2
unnamed: D28.A, R47.1
unnamed: C4.1, IC12.6 (OUT), R41.1
unnamed: C4.2, C109.1, D5.C, D6.A, IC12.2 (-IN), R45.2, R46.1
unnamed: C111.1, C131.1, IC11.3 (+IN), R5.1
unnamed: C3.1, IC11.6 (OUT), R42.1
unnamed: R39.1, U$48.3 (E2)
unnamed: D23.A, U$48.1 (E1)
unnamed: R37.2, U$49.3 (E2)
unnamed: D22.C, U$49.1 (E1)
V+: C13.1, C106.+, C108.1, C132.1, IC10.2 (IN), IC11.7 (V+), R44.2, R46.2, R47.2, U$1.3 (E), U$2.E, X2.1
V+2: C35.+, C37.1, C44.1, C51.1, IC4.2 (IN), IC5.7 (V+), R30.2, R32.2, R33.2, U$13.3 (E), U$14.E, X6.1
V-: C14.2, C107.-, C109.2, C130.2, IC12.4 (V-), R45.1, R48.1, U$3.3 (E), U$4.E, X2.3
V-2: C36.-, C38.2, C42.2, C52.2, IC6.4 (V-), R31.1, R34.1, U$15.3 (E), U$16.E, X6.3
VIN+: B1.+, C1.+, C9.1, C126.+, D22.A, R4.1, R37.1, U$1.2 (C), U$2.C
VIN+2: B5.+, C40.+, C45.+, C49.1, D18.A, R23.1, R50.1, U$13.2 (C), U$14.C
VIN-: B2.-, C2.-, C10.2, C128.-, D23.C, R3.2, R39.2, U$3.2 (C), U$4.C
VIN-2: B6.-, C41.-, C46.-, C50.2, D19.C, R25.2, R49.2, U$15.2 (C), U$16.C
